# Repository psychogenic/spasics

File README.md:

# SpASICs
----------

Scratch repo for work, thoughts and notes about the spasics project: sending an ASIC to space!

It may be possible for [Tiny Tapeout](https://tinytapeout.com/) to include an experiment module aboard a [pocketQube](https://en.wikipedia.org/wiki/PocketQube) class satellite, so am collecting preliminary work on this here, in the hopes of getting ideas and feedback.

## Basic Requirements

Details on the objectives and requirements are all in the PRD, [SpASICs: ASIC Modular satellite experimentation board requirements](doc/SpASICsRequirements.md).  This is also available as [a PDF](doc/spasics.pdf).

## TODO

In addition to feedback on the PRD itself, the following require further work, feedback and ideas:

   * A means to safely run arbitrary, user-submitted, experiments.  Short version is we can't hang, we can't die, no matter what.  The proposed/sample implementation is [experiment_runner.py](python/experiment_runner.py) 
   
   * A complete API for commands and responses from the base system to our module.  Details on that are in [Experiment Module API](doc/ExperimentModuleAPI.md).
   
   * A means to safely update the system (ideally this would go all the way to the uPython firmware itself but, owing to bw constraints, this may be restricted to everything above that layer).  I would like to see something like a 2-slot OTA system, where we have everything in two places, run from slot A, update to slot B, attempt to run from slot B and revert to slot A on failure otherwise slot B becomes primary... that sort of thing.  TBD in [Firmware Updates](doc/FirmwareUpdates.md).
   
   * A byte-efficient means of patching the system.  Some updates may only be changes to a few lines of code, what is the most effective means of transmitting this data?  Also TBD in [Firmware Updates](doc/FirmwareUpdates.md).
   
   * Resilient data stores for outgoing data queues, log data, scheduling information etc 
   
   * Implementation code for above, once defined
   
   * More TODOs

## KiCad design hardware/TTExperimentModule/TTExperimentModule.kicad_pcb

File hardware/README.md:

# Experiment Module Hardware

A single PCB created to host both the ASIC and the platform for the Experiment Run and Data Collection Framework (an RP2040) for inclusion within the [pocketQube](https://en.wikipedia.org/wiki/PocketQube) class satellite.

In addition to the meeting requirements related to being included in the launch (e.g. a 3mm height maximum, no silk screen, etc), a primary goals were to

  * provide a seamless path to running [SDK](https://github.com/TinyTapeout/tt-micropython-firmware) and existing ASIC project code with minimal disruption; and
  
  * reuse as much prior-tested components and circuitry
  
Thus, to the maximum extent possible, parts and pinouts were preserved, while major schematic elements were reproduced from the [demoboard](https://github.com/tinytapeout/tt-demo-pcb) and [ASIC breakout](https://github.com/tinyTapeout/breakout-pcb).

## Board 

[Explore the design online using KiCanvas](https://kicanvas.org/?github=https%3A%2F%2Fgithub.com%2Fpsychogenic%2Fspasics%2Ftree%2Fmain%2Fhardware%2FTTExperimentModule)

The basic schematic is

and you can consult the entire schematic in [the PDF](image/TTExperimentModule.pdf).

The PCB is 45x30mm and is mainly concerned with routing I/O around the big hole in the middle of the board.

## Sources

The entire [KiCad](https://www.kicad.org/) project is in [TTExperimentModule](./TTExperimentModule)

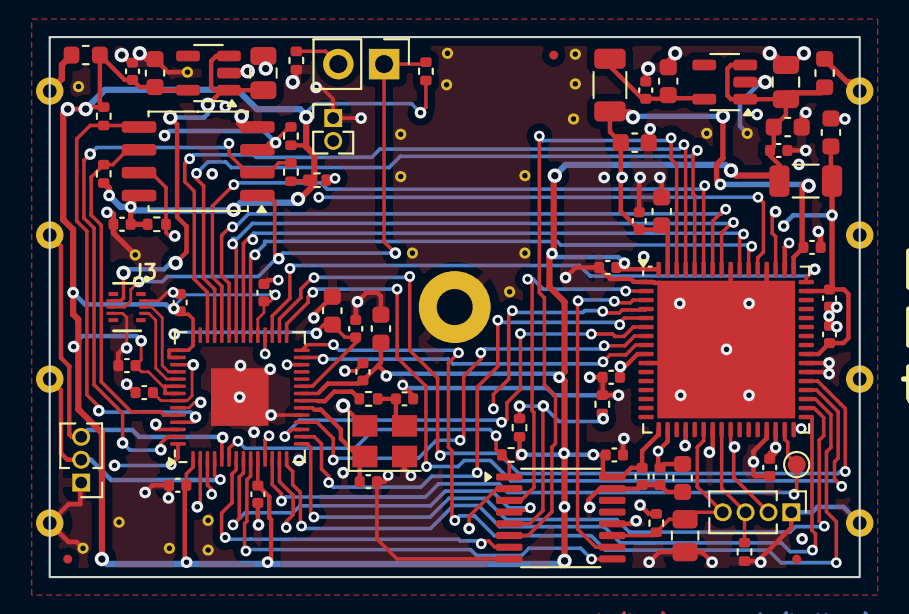
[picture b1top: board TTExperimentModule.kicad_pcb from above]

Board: 4 copper layers, 45.0 x 30.0 mm, 92 parts (0 on the bottom side), 57 nets.

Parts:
C1, C5: 10uF; C_0805_2012Metric
C2, C6, C27, C28: 1uF; C_0603_1608Metric
C3, C4, C7, C31, C32, C33, C34, C35, C36, C37, C38, C39: 100nF; C_0402_1005Metric
C8, C12, C14, C15, C16: C_1u_0603_50V; C_0603_1608Metric
C17, C18, C19, C20, C21, C22, C23, C24, C25, C26: 0.1uf; C_0402_1005Metric
C29, C30: 6pF; C_0402_1005Metric
FB1, FB2: FerriteBead_Small; L_0603_1608Metric
FID1, FID2, FID3: Fiducial; Fiducial_0.5mm_Mask1mm
J1: Conn_01x03; PinHeader_1x03_P1.27mm_Vertical
J2: Conn_01x02; PinHeader_1x02_P2.54mm_Vertical
J3: 5050700622; CONN_505070-0622_MOL
J5: Conn_01x04; PinHeader_1x04_P1.27mm_Vertical
J6: Conn_01x02; PinHeader_1x02_P1.27mm_Vertical
PCB1: NMHH-1 3PQ; pocketqube_experiment
R1, R2, R3, R4, R5, R13, R15, R16, R17, R18, R19: 10k; R_0402_1005Metric
R6, R11, R14: 1k; R_0402_1005Metric
R7, R8: 0R; R_1206_3216Metric
R9: 1k; R_0805_2012Metric
STITCH1, STITCH1#2, STITCH1#3, STITCH1#4, STITCH1#5, STITCH1#6, STITCH1#7, STITCH1#8, STITCH1#9, STITCH1#10, STITCH1#11, STITCH1#12, STITCH1#13, STITCH1#14, STITCH1#15, STITCH1#16, STITCH1#17, STITCH1#18, STITCH1#19, STITCH1#20, STITCH1#21: StitchingVia-0.3mm
TP1: TestPoint; TestPoint_Pad_D1.0mm
U1: 74CBTLV3257; TSSOP-16_4.4x5mm_P0.65mm
U2: AP2112K-1.8; SOT-23-5
U3: AP2112K-3.3; SOT-23-5
U4: Openframe_QFN_TT06_REV2; QFN-64-1EP_9x9mm_P0.5mm_EP7.65x7.65mm
U5: RP2040; QFN-56-1EP_7x7mm_P0.4mm_EP3.2x3.2mm
U6: W25Q32JVSS; SOIC-8_5.3x5.3mm_P1.27mm
Y1: 12.0MHz; Crystal_SMD_3225-4Pin_3.2x2.5mm

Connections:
+1V8: C2.1, C3.1, R8.2, U2.5 (VOUT)
+3V3: C1.1, C4.1, C6.1, C7.1, C8.1, C17.2, C21.2, C22.2, C28.1, C31.2, C32.1, C33.1, C34.1, C37.1, C38.1, C39.1, FB1.1, FB2.2, R1.1, R3.2, R4.1, R5.1, R7.2, R13.1, R15.1, R16.1, R17.1, R18.1, R19.1, U1.16 (VCC), U2.1 (VIN), U2.3 (EN), U3.5 (VOUT), U4.17 (vddio), U4.64 (vddio), U5.1 (IOVDD), U5.10 (IOVDD), U5.22 (IOVDD), U5.33 (IOVDD), U5.42 (IOVDD), U5.43 (ADC_AVDD), U5.44 (VREG_IN), U5.48 (USB_VDD), U5.49 (IOVDD), U6.8 (VCC)
+5V: C5.1, J3.2, U3.1 (VIN), U3.3 (EN)
/ASIC/vccd_all: C14.1, C15.1, C16.1, C18.2, C19.1, C20.2, R8.1, U4.18 (vccd), U4.49 (vccd1), U4.63 (vccd2)
/ASIC/vdda_all: C12.1, C23.1, C24.1, C25.1, C26.2, R7.1, U4.9 (vdda2), U4.30 (vdda), U4.40 (vdda1), U4.47 (vdda1)
/RP2040/DVDD: C27.2, C35.1, C36.1, U5.23 (DVDD), U5.45 (VREG_VOUT), U5.50 (DVDD)
/RP2040/QSPI_CLK: R19.2, U5.52 (QSPI_SCLK), U6.6 (CLK)
/RP2040/QSPI_SD0: R17.2, U5.53 (QSPI_SD0), U6.5 (DI(IO0))
/RP2040/QSPI_SD1: R18.2, U5.55 (QSPI_SD1), U6.2 (DO(IO1))
/RP2040/QSPI_SD2: R15.2, U5.54 (QSPI_SD2), U6.3 (IO2)
/RP2040/QSPI_SD3: R16.2, U5.51 (QSPI_SD3), U6.7 (IO3)
/RP2040/RUN: J6.2, R13.2, U5.26 (RUN)
/RP2040/xin: C29.1, U5.20 (XIN), Y1.1
/RP2040/xout: R14.2, U5.21 (XOUT)
/RP2040/xoutr: C30.1, R14.1, Y1.3
/ctrl_ena: J5.4, R3.1, R9.1, U1.11, U4.22 (ctrl_ena)
/ctrl_sel_inc: J5.3, R2.1, U1.2, U4.24 (ctrl_sel_inc)
/mux_sel: R4.2, U1.1 (S), U5.6 (GPIO4)
/out0_~rst: U1.7, U5.7 (GPIO5)
/out1_inc: U1.4, U5.8 (GPIO6)
/out2_ena: U1.9, U5.9 (GPIO7)
/proj_clk: U4.50 (clk), U5.2 (GPIO0)
/ui_in0: TP1.1, U4.31 (ui_in[0]), U5.12 (GPIO9)
/ui_in1: U4.32 (ui_in[1]), U5.13 (GPIO10)
/ui_in2: U4.33 (ui_in[2]), U5.14 (GPIO11)
/ui_in3: U4.34 (ui_in[3]), U5.15 (GPIO12)
/ui_in4: U4.35 (ui_in[4]), U5.28 (GPIO17)
/ui_in5: U4.36 (ui_in[5]), U5.29 (GPIO18)
/ui_in6: U4.37 (ui_in[6]), U5.30 (GPIO19)
/ui_in7: U4.48 (ui_in[7]), U5.31 (GPIO20)
/uio0: U4.53 (uio[0]), U5.32 (GPIO21)
/uio1: U4.54 (uio[1]), U5.34 (GPIO22)
/uio2: U4.55 (uio[2]), U5.35 (GPIO23)
/uio3: U4.57 (uio[3]), U5.36 (GPIO24)
/uio4: U4.58 (uio[4]), U5.37 (GPIO25)
/uio5: U4.59 (uio[5]), U5.38 (GPIO26_ADC0)
/uio6: U4.60 (uio[6]), U5.39 (GPIO27_ADC1)
/uio7: U4.61 (uio[7]), U5.40 (GPIO28_ADC2)
/uo_out0: U1.6, U4.62 (uo_out[0])
/uo_out1: U1.3, U4.2 (uo_out[1])
/uo_out2: U1.10, U4.3 (uo_out[2])
/uo_out3: U4.4 (uo_out[3]), U5.11 (GPIO8)
/uo_out4: U4.5 (uo_out[4]), U5.16 (GPIO13)
/uo_out5: U4.6 (uo_out[5]), U5.17 (GPIO14)
/uo_out6: U4.7 (uo_out[6]), U5.18 (GPIO15)
/uo_out7: U4.8 (uo_out[7]), U5.27 (GPIO16)
/vin1: FB1.2, PCB1.1 (VDD)
/vin2: FB2.1, PCB1.8 (VDD)
/~ctrl_sel_rst: J5.2, R1.2, R11.1, U1.5, U4.25 (ctrl_sel_rst_n)
/~proj_rst: U4.51 (rst_n), U5.3 (GPIO1)
GND: C1.2, C2.2, C3.2, C4.2, C5.2, C6.2, C7.2, C8.2, C12.2, C14.2, C15.2, C16.2, C17.1, C18.1, C19.2, C20.1, C21.1, C22.1, C23.2, C24.2, C25.2, C26.1, C27.1, C28.2, C29.2, C30.2, C31.1, C32.2, C33.2, C34.2, C35.2, C36.2, C37.2, C38.2, C39.2, J1.1, J3.1, J3.6, J5.1, J6.1, PCB1.4 (GND), PCB1.5 (GND), PCB1.9 (GND), R2.2, R6.2, R9.2, R11.2, STITCH1.1, STITCH1#2.1, STITCH1#3.1, STITCH1#4.1, STITCH1#5.1, STITCH1#6.1, STITCH1#7.1, STITCH1#8.1, STITCH1#9.1, STITCH1#10.1, STITCH1#11.1, STITCH1#12.1, STITCH1#13.1, STITCH1#14.1, STITCH1#15.1, STITCH1#16.1, STITCH1#17.1, STITCH1#18.1, STITCH1#19.1, STITCH1#20.1, STITCH1#21.1, U1.8 (GND), U1.12, U1.15 (~OE), U2.2 (GND), U3.2 (GND), U4.1 (vssa2), U4.10 (vssd2), U4.20 (vssa), U4.23 (vssd), U4.29 (vssio), U4.38 (vssa1), U4.39 (vssd1), U4.52 (vssa1), U4.56 (vssio), U4.65 (ThermalPad), U5.19 (TESTEN), U5.57 (GND), U6.4 (GND), Y1.2, Y1.4
unnamed: J2.2, R6.1
SCL1: J1.3, PCB1.2 (SCL), U5.5 (GPIO3)
SDA1: J1.2, PCB1.3 (SDA), U5.4 (GPIO2)
boot_mode: J2.1, J3.4, R5.2, U5.56 (QSPI_SS), U6.1 (~CS)
usb_d+: J3.5, U5.47 (USB_DP)
usb_d-: J3.3, U5.46 (USB_DM)

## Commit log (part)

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2025-03-28 preliminary thoughts
2025-03-28 fw update notes
2025-03-28 queued data fetch
2025-03-29 assumption req for i2c bus malfunction heartbeat/timeout
2025-04-13 TT Experiment board hardware
2025-04-13 kicanvas link fix
2025-04-15 reduced-height flash (dual footprint), layout rework, markings
2025-04-21 BOM updates for spaaaaaace
2025-04-21 fatter support pads for 5050660622
2025-04-21 basic 2-core spasic framework
2025-04-28 Mega system, smashing stack
2025-04-29 Major refactor and simplification, basic working
2025-04-29 Running experiments on core1, real time status queries and responses
2025-04-29 main cleanup
2025-04-29 reporting exceptions in status and ttboard precompile for bigger stacks
2025-04-29 attempt to run without thread, still smashing stack
2025-04-29 Simple working (?)
2025-04-29 cleanup
2025-04-29 more cleanup
2025-04-29 watchdog enable and cleanup
2025-04-29 Multiple experiment framework, running
2025-04-29 Experiment list and failing exp
2025-04-29 disable wdog for dev
2025-04-29 more well behaved sim client
2025-04-29 TT06 DB firmware with i2cslave and latest spasic driver
2025-04-29 Experiment parameters, keep_running/termination and stack management
2025-04-29 Experiment params/args and termination control
2025-04-29 client test abort command
2025-04-29 Experiment dynamic settings and documentation
2025-04-29 Experiment argument bytes handling
2025-04-29 Queueing reports of completed experiments
2025-04-29 more complete experiment report, with completed status and exception id
2025-04-29 using stack settings in uPython distro rather than tweaking here
2025-04-29 Reboot support
2025-04-29 some randomness to test runs
2025-04-29 Watchdog enabled, no print() in isr cb (!), and quicker queueing of exp run response
2025-04-29 docs for python system and testing
2025-04-29 doc tweak
2025-04-29 docs for sat simulator
2025-04-29 actually respecting args in ctor
2025-04-29 harden, safer incoming (len checked) and better pings
2025-04-29 info about using TT06 demoboard for testing
2025-04-29 stress test includes reboots and forever loops/abort
2025-04-30 tracking of timesync messages, reporting unexpected exceptions, inline docs for server
2025-04-30 error message parsing bug fix
2025-04-30 More informative uncaught exception messaging
2025-04-30 Reducing mem usage
2025-05-01 test experiment fixes and improvements
2025-05-01 Ensuring demoboard always in ASIC_RP_CONTROL prior to launching an experiment
2025-05-01 i2c simulation device for dev
2025-05-01 i2c and general debug assists
2025-05-01 Preliminary version of FS update system
2025-05-01 File upload and client rework
2025-05-05 Experiment writer's guide
2025-05-06 spasics bundled firmware
2025-05-06 reboots without watchdog aren't great
2025-05-06 Pure polling i2c slave device (working!?), 0x00 empty bytes
2025-05-07 experiments merge
2025-05-08 polling and basic working shipped
2025-05-08 new experiments
2025-05-08 refactor and reorg
2025-05-09 better filesystem support
2025-05-09 client-side file uploads and management
2025-05-09 experiment immediate result command
2025-05-09 experiment immediate result and error code interp.
2025-05-09 Removed limit to experiment arguments
2025-05-09 Inline docs and full function of new experiment args system
2025-05-09 better packet dumper collection of data and full sim var get/set
2025-05-09 clear arg swap or aborts
2025-05-09 API doc update
2025-05-09 more contribs to lottery
2025-05-09 ResponseInfo response
2025-05-09 info responses, time sync track, clean-up and settings for production/delivery
2025-05-09 info packets, experiment monitoring, quiet mode
2025-05-09 missing version file
2025-05-09 more experiments!
2025-05-09 Sat sim result interpretation support
2025-05-09 info command doc
2025-05-09 packet dumper saved packets size adjust
2025-05-09 updated sample packetdumper interaction
2025-05-09 Experiment run queue support
2025-05-09 new experiment!
2025-05-09 Final experiment included for ship 2
2025-05-14 ExperimentModuleAPI: Fix command type byte typo
2025-05-27 new experiments batch import
2025-05-27 made experiments available
2025-05-27 the forgotten experimental child
2025-05-27 extra in data poll
2025-05-27 prettification, finer ctrl and util func for i2c client test
2025-05-27 version bump and i2c p-u off for deployment
2025-05-27 memory saver delux: if/else loading of experiment modules
2025-05-27 memory saving/defrag attempt (results paltry)
2025-05-27 more randomy randint and bytearray for results
2025-05-27 0.9.9 firmware bundle
2025-05-27 firmware cleanup
2025-05-27 Experiment list reworked with Troy's cool (i.e. working) importer
2025-05-27 Memory block reservations to try and help with defrag
2025-05-28 Memory reserve liberation
2025-05-28 0.9.9b fw
2025-05-28 more contribs
2025-05-28 microcotb begone
2025-05-28 microcotb begone pII
2025-05-28 fw with new and improved cejmu experiment
2025-06-15 merged 3 PRs from spasic_experiment_testing
2025-06-15 rp2_temperature experiment added to available
2025-06-15 Made rp2 temp exp interruptable
2025-06-16 tt_um_CKPope_top x/y position controller experiment
2025-06-25 final experiments, loaded and tested
2025-06-25 safemode settings, memory tweaks, and full fallback module support
2025-06-25 pre-built v1.0 UF2
2025-07-01 Experiment module request scheduling
2025-07-28 better client packet chunking
2025-07-28 re-add of dropped SEU experiment
2025-07-28 auto result, status and info packets, on sat poll schedule
2025-07-28 v1.1.0 -- launch ready
2025-07-28 old firmware removal
2025-07-31 enabled parsing of results from sat
2025-07-31 augmented trans gen for better CSV output
2025-11-26 mods to exp run spreadsheet and docs
2026-01-06 sat telemetry parser
2026-01-06 made transaction generator easier to use on command line
2026-01-06 module commands requested log
2026-01-08 better telemetry parsing
2026-01-08 telemetry parser abstractions
2026-01-08 mv telemetry stuff to own package
2026-01-09 Telemetry parser refactor
2026-01-09 Add parser for TinyQV experiments
2026-01-09 full loop local flight model and better parser
2026-01-09 tinyQV status parser override
2026-01-09 TinyQV parser: Handle short status
2026-01-10 CSV output for parsed telemetry
2026-01-10 commands request 003
2026-01-10 First responses from LEO!
2026-01-10 request log update
2026-01-14 better csv exports from parsing telemetry
2026-01-14 sat request 003 responses received
2026-01-14 add QubitText decompressor to result parser
    This commit implements the `resultparse_tt_um_qubitbytes_alive` function in `report_interpreter.py` to handle the `tt_um_qubitbytes_alive` experiment results.
2026-01-14 Fix return message in report_interpreter.py
2026-01-14 re-parse with tt_um_qubitbytes_alive result interpreter
2026-03-25 experiment run 004 request and responses
2026-06-15 HUNITY websocket API support and CLI

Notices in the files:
hardware/TTExperimentModule/TTExperimentModule.kicad_pcb:
(C) 2025 Pat Deegan
